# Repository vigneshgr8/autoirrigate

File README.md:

# AutoIrrigate
A device that can automate the irrigation process for your farm. You can install this with your current systems which has a high power motor with a starter.

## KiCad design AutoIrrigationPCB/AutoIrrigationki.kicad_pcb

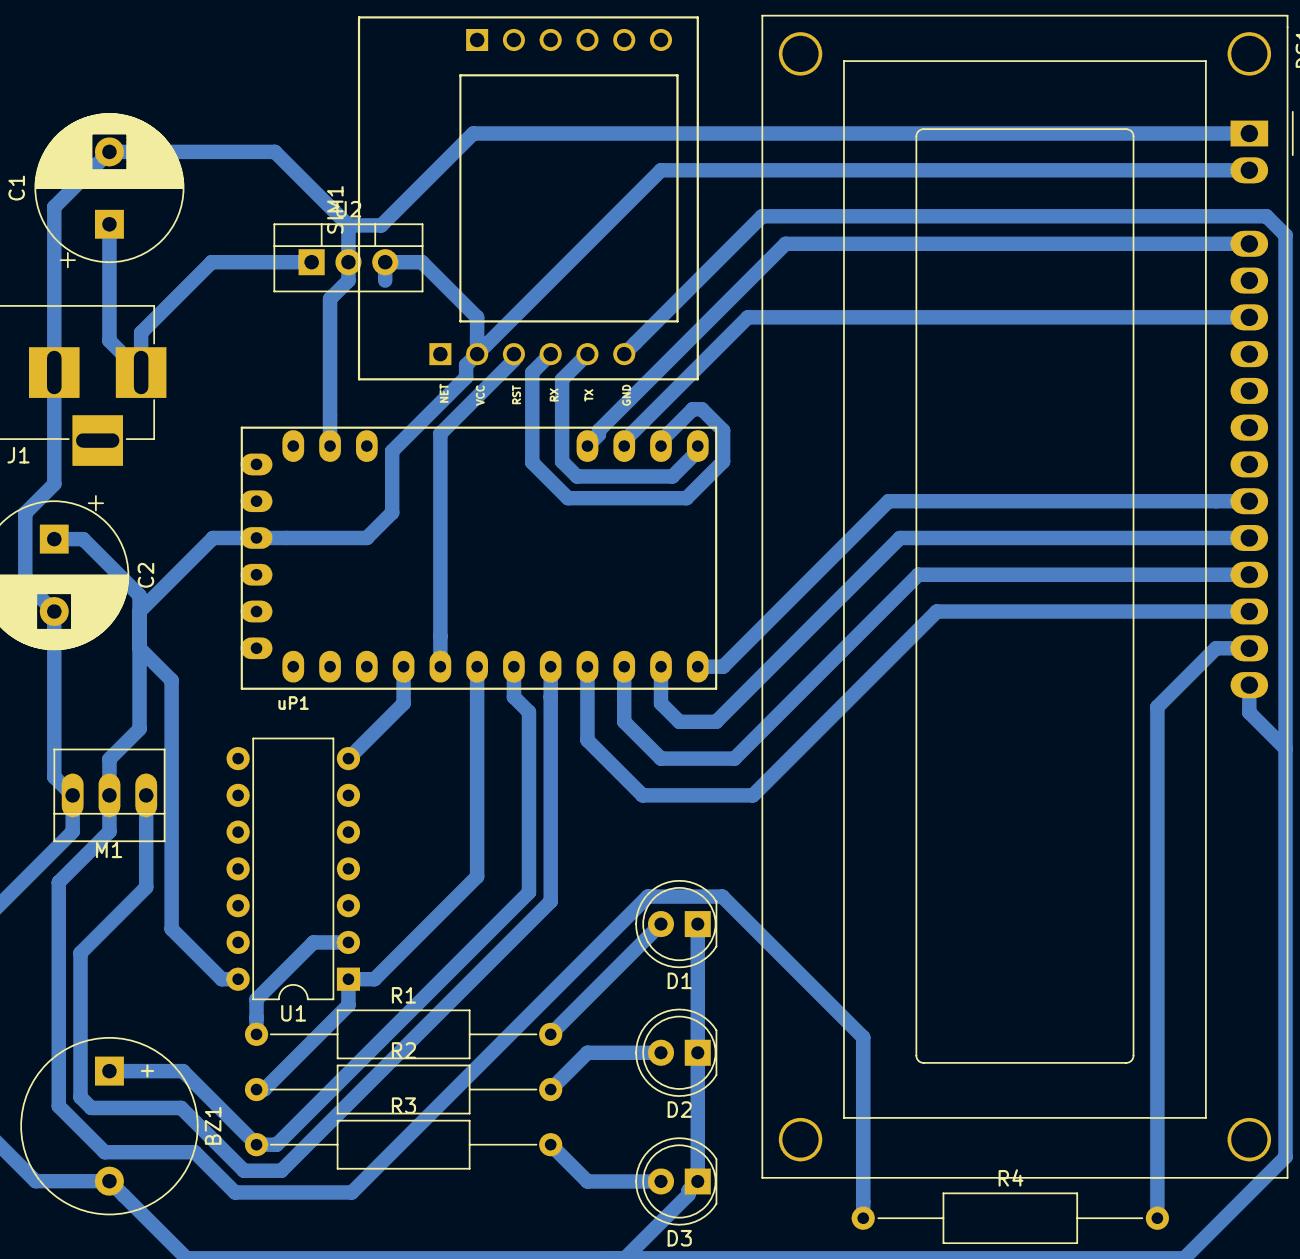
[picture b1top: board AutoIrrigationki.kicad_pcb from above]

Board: 2 copper layers, 17 parts (0 on the bottom side), 21 nets.

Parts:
BZ1: Buzzer; Buzzer_12x9.5RM7.6
C1, C2: CP; CP_Radial_D10.0mm_P5.00mm
D1, D2, D3: LED; LED_D5.0mm
DS1: LCD16X2; WC1602A
J1: BARREL_JACK
M1: Motor_Servo; PINHEAD1-3
R1, R2, R3, R4: R; R_Axial_DIN0309_L9.0mm_D3.2mm_P20.32mm_Horizontal
SIM1: SIM800L; Sim800L
U1: 74LS04; DIP-14_W7.62mm
U2: 7805; TO-220_Vertical
uP1: ARDUPROMINI-RESCUE-Main_Board; pro_mini

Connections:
GND: BZ1.2, C1.2, C2.2, D1.1, D2.1, D3.1, DS1.1, DS1.16, J1.2, M1.3, SIM1.6, U2.2, uP1.23
unnamed: BZ1.1, R3.1, uP1.7
unnamed: C1.1, J1.1, U2.1
unnamed: C2.1, DS1.2, M1.2, R4.1, SIM1.2, U1.14, U2.3, uP1.31
unnamed: D1.2, R1.2
unnamed: D2.2, R2.2
unnamed: D3.2, R3.2
unnamed: DS1.4, uP1.16
unnamed: DS1.6, uP1.15
unnamed: DS1.11, uP1.12
unnamed: DS1.12, uP1.11
unnamed: DS1.13, uP1.10
unnamed: DS1.14, uP1.9
unnamed: DS1.15, R4.2
unnamed: M1.1, uP1.8
unnamed: R1.1, U1.2
unnamed: R2.1, U1.1, uP1.6
unnamed: SIM1.3, uP1.5
unnamed: SIM1.4, uP1.14
unnamed: SIM1.5, uP1.13
unnamed: U1.7, uP1.4

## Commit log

2018-05-28 Arduino ino file
    This contains the main arduino program
2018-05-28 Photos of hardware and it's working
    This is the one I made and you can build it easily at a cost of less than 1000₹ (~15$)
2018-05-28 Schematic and PCD
    This folder contains the schematics and the PCB designs. There are some mistakes with the PCB design they are as follows
    There is no GSM module being used, instead it's an RTC so the whole SIM800L section can be discarded.
    New connections should be made to the SDA and SDL pins.
    The LCD doesn't have a pot so that should also be added
    The PCB design has been done in KiCAD. I did it in linux.
2018-05-28 KiCAD User Library
    This is an Arduino pro mini user library that I had modified for the model of arduino that I use. add it to the project file
